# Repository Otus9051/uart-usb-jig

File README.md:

# MicroUSB to TTL to USB converter
## Should work with almost any Samsung device

- Connectors:
    - Micro USB B Male
    - USB A 2.0 Female
 
- Utitlizes CP2102N as the Serial to USB convertor
- ID pin of Micro USB B Male is connected to 619K Ohm Resistor
- 619K Ohm Resistance triggers Samsung MUIC to switch to USB UART mode

- LCSC Part Numbers included in Bill of Materials
- Pulls 5V from USB A, Micro USB B gets 3.3V from CP2102 VDD (refer documentation)

P.S.: This is my first try at making a PCB, please let me know any issues if you come across any

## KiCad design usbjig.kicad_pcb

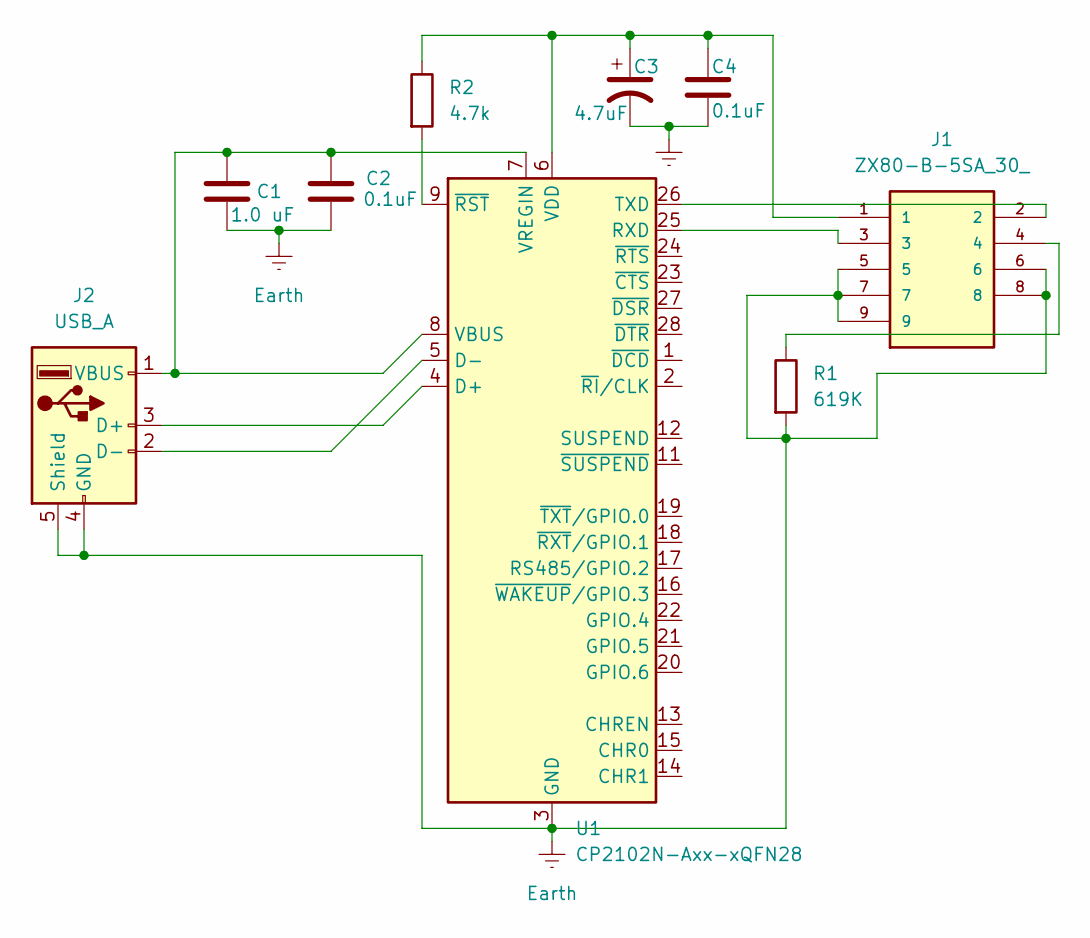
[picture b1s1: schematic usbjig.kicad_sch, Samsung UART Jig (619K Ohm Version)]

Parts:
C1: 1.0 uF; C_0201_0603Metric; LCSC C1848
C2, C4: 0.1uF; CP_Elec_4x5.4; LCSC C271438
C3: 4.7uF; CP_Elec_4x5.4; LCSC C271399
J1: ZX80-B-5SA_30_; ZX80B5SA30; LCSC C598212
J2: USB_A; USB_A_Molex_67643_Horizontal; LCSC C293351
R1: 619K; R_0201_0603Metric; LCSC C3015991
R2: 4.7k; R_0201_0603Metric
U1: CP2102N-Axx-xQFN28; QFN-28-1EP_5x5mm_P0.5mm_EP3.35x3.35mm; LCSC C964632

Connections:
Earth: C1.2, C2.2, C3.2, C4.2, J1.5, J1.6, J1.7, J1.8, J1.9, J2.4 (GND), J2.5 (Shield), R1.2, U1.3 (GND), U1.29 (GND)
unnamed: J1.4, R1.1
unnamed: J2.3 (D+), U1.4 (D+)
unnamed: J2.2 (D-), U1.5 (D-)
unnamed: C1.1, C2.1, J2.1 (VBUS), U1.7 (VREGIN), U1.8 (VBUS)
unnamed: J1.3, U1.25 (RXD)
unnamed: J1.2, U1.26 (TXD)
unnamed: C3.1, C4.1, J1.1, R2.1, U1.6 (VDD)
unnamed: R2.2, U1.9 (~RST)

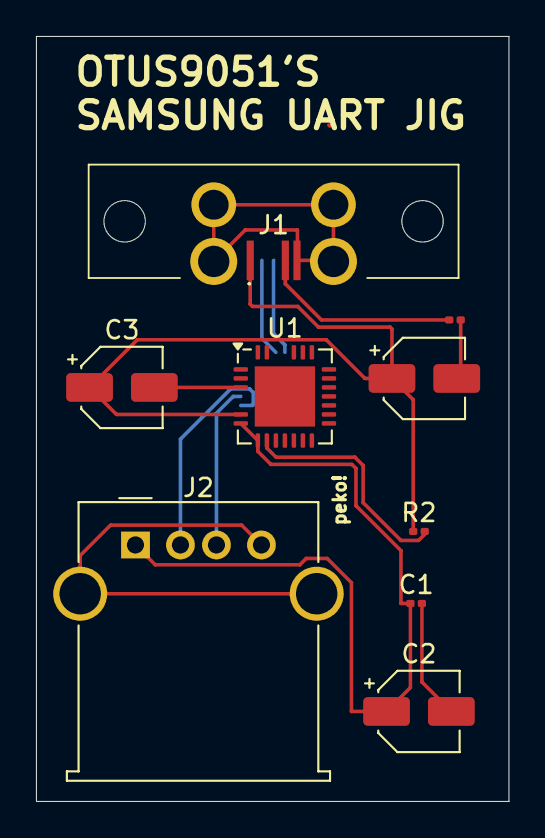
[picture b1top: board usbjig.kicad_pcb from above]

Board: 2 copper layers, 26.2 x 42.5 mm, 9 parts (0 on the bottom side), 9 nets.

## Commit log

2024-06-28 Upload PCB Stuff
